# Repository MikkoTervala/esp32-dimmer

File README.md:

# esp32-dimmer

PCB for the ESP32 WROOM module, with power supply and up to six mosfets for LED strip dimming.

# 2023 Model

## Specifications

* Uses the ESP32-C3-WROOM-02-H4 microcontroller module
* Built in USB C connector for programming
* Designed to be made with SMD assembly
* 12 to 24V
* Designed for 5A single channel or 10A combined.

## Notes

* Ordering 10 PCB's with SMD assembly not including ESP32 cost 65€
* Ordering 10 ESP32-C3 modules and regulators cost 43€ 

## Next version ideas

* Add power LED
* Move 24V and GND pins to the middle of connector for shorter routing
* Expose all unused GPIO's as SMD test points

# 2020 Model

## Specifications

* 12 or 24V
* Designed for 5A single channel or 10A combined with a low cost 1 oz PCB.
* Can be used with ESP32-WROOM-32 module or the DOIT Esp32 DevKit available from china.
* Can be used with CUI VXO7803-500 DC-DC converter or with "mini power supply module 3A" available from china.
* Fits inside square european electrical box.

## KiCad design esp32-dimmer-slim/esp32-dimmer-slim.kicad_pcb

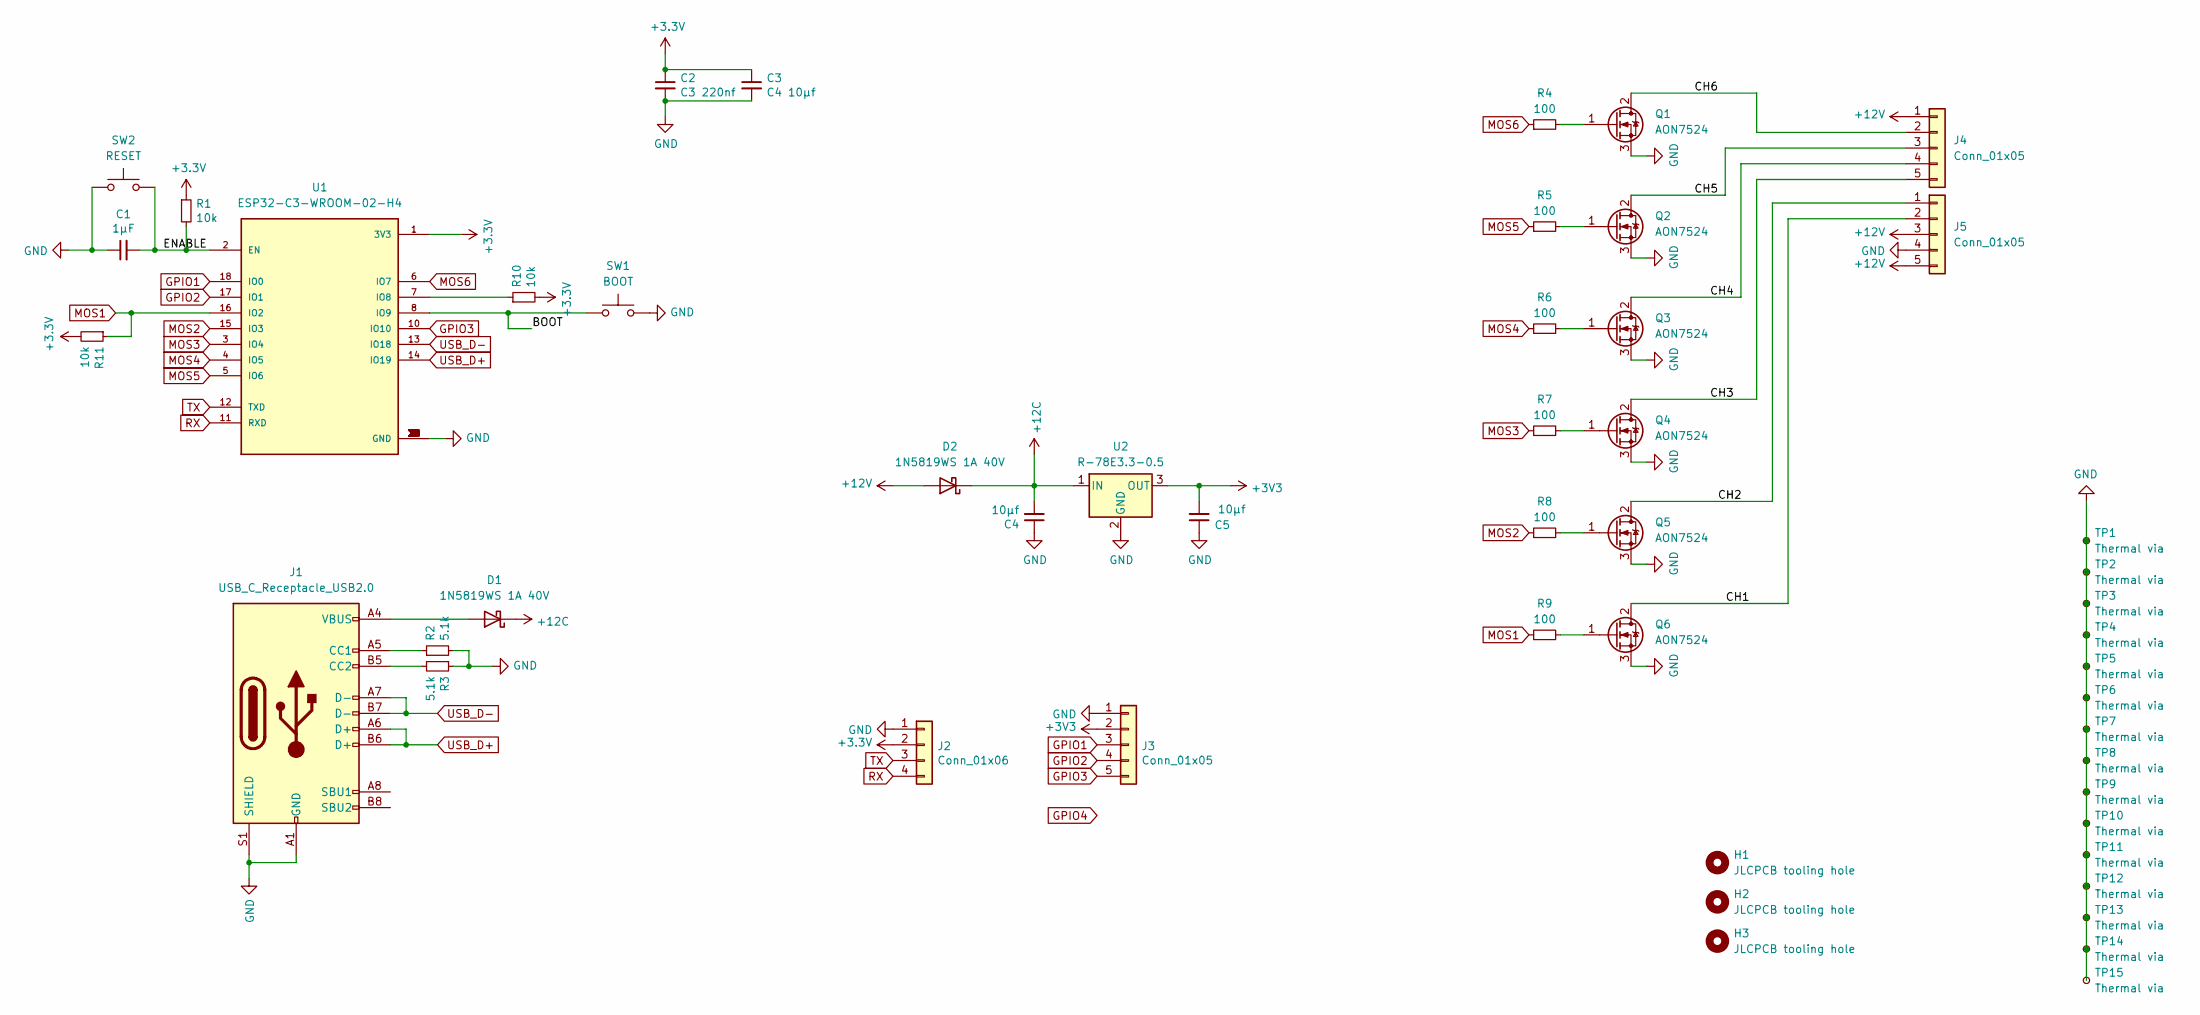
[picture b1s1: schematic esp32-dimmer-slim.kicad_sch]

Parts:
C1: 1µF; C_0603_1608Metric; LCSC Part # C15849
C2: C3 220nf; C_0603_1608Metric; LCSC Part # C21120
C3: C4 10µf; C_1206_3216Metric; LCSC Part # C13585
C4, C5: 10µf; C_1206_3216Metric; LCSC Part # C13585
D1, D2: 1N5819WS 1A 40V; D_SOD-323; LCSC Part # C191023
H1, H2, H3: JLCPCB tooling hole
J1: USB_C_Receptacle_USB2.0; TYPE-C-31-M-12; LCSC Part # C165948
J2: Conn_01x06; PinHeader_1x04_P2.54mm_Vertical
J3: Conn_01x05; PinHeader_1x05_P2.54mm_Vertical
J4, J5: Conn_01x05; CONN_2604-1105_WAG
Q1, Q2, Q3, Q4, Q5, Q6: AON7524; TRANS_AON7403; LCSC Part # C431195
R1, R10, R11: 10k; R_0603_1608Metric; LCSC Part # C25804
R2, R3: 5.1k; R_0603_1608Metric; LCSC Part # C23186
R4, R5, R6, R7, R8, R9: 100; R_0603_1608Metric; LCSC Part # C22775
SW1: BOOT; SW_Push_1P1T_XKB_TS-1187A; LCSC Part # C318884
SW2: RESET; SW_Push_1P1T_XKB_TS-1187A; LCSC Part # C318884
TP1, TP2, TP3, TP4, TP5, TP6, TP7, TP8, TP9, TP10, TP11, TP12, TP13, TP14, TP15: Thermal via; thermal via
U1: ESP32-C3-WROOM-02-H4; MODULE_ESP32-C3-WROOM-02-H4; LCSC Part # C2934560
U2: R-78E3.3-0.5; Converter_DCDC_RECOM_R-78E-0.5_THT

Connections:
+12C: C4.2, D1.1 (K), D2.1 (K), U2.1 (IN)
+12V: D2.2 (A), J4.1, J5.3, J5.5
/BOOT: SW1.1, U1.8 (IO9)
/CH1: J5.2, Q6.2 (D)
/CH2: J5.1, Q5.2 (D)
/CH3: J4.5, Q4.2 (D)
/CH4: J4.4, Q3.2 (D)
/CH5: J4.3, Q2.2 (D)
/CH6: J4.2, Q1.2 (D)
/ENABLE: C1.2, R1.2, SW2.2, U1.2 (EN)
GND: C1.1, C2.2, C3.2, C4.1, C5.1, J1.A1 (GND), J1.A12 (GND), J1.B1 (GND), J1.B12 (GND), J1.S1 (SHIELD), J2.1, J3.1, J5.4, Q1.3 (S), Q2.3 (S), Q3.3 (S), Q4.3 (S), Q5.3 (S), Q6.3 (S), R2.2, R3.1, SW1.2, SW2.1, TP1.1, TP2.1, TP3.1, TP4.1, TP5.1, TP6.1, TP7.1, TP8.1, TP9.1, TP10.1, TP11.1, TP12.1, TP13.1, TP14.1, TP15.1, U1.9 (GND), U1.19 (GND), U1.20 (GND), U1.21 (GND), U1.22 (GND), U1.23 (GND), U1.24 (GND), U1.25 (GND), U1.26 (GND), U1.27 (GND), U1.28 (GND), U1.29 (GND), U1.30 (GND), U1.31 (GND), U1.32 (GND), U1.33 (GND), U1.34 (GND), U1.35 (GND), U1.36 (GND), U1.37 (GND), U1.38 (GND), U1.39 (GND), U2.2 (GND)
GPIO1: J3.3, U1.18 (IO0)
GPIO2: J3.4, U1.17 (IO1)
GPIO3: J3.5, U1.10 (IO10)
MOS1: R9.1, R11.1, U1.16 (IO2)
MOS2: R8.1, U1.15 (IO3)
MOS3: R7.1, U1.3 (IO4)
MOS4: R6.1, U1.4 (IO5)
MOS5: R5.1, U1.5 (IO6)
MOS6: R4.1, U1.6 (IO7)
unnamed: D1.2 (A), J1.A4 (VBUS), J1.A9 (VBUS), J1.B4 (VBUS), J1.B9 (VBUS)
unnamed: J1.A5 (CC1), R2.1
unnamed: J1.B5 (CC2), R3.2
unnamed: Q1.1 (G), R4.2
unnamed: Q2.1 (G), R5.2
unnamed: Q3.1 (G), R6.2
unnamed: Q4.1 (G), R7.2
unnamed: Q5.1 (G), R8.2
unnamed: Q6.1 (G), R9.2
unnamed: R10.1, U1.7 (IO8)
RX: J2.4, U1.11 (RXD)
TX: J2.3, U1.12 (TXD)
USB_D+: J1.A6 (D+), J1.B6 (D+), U1.14 (IO19)
USB_D-: J1.A7 (D-), J1.B7 (D-), U1.13 (IO18)

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
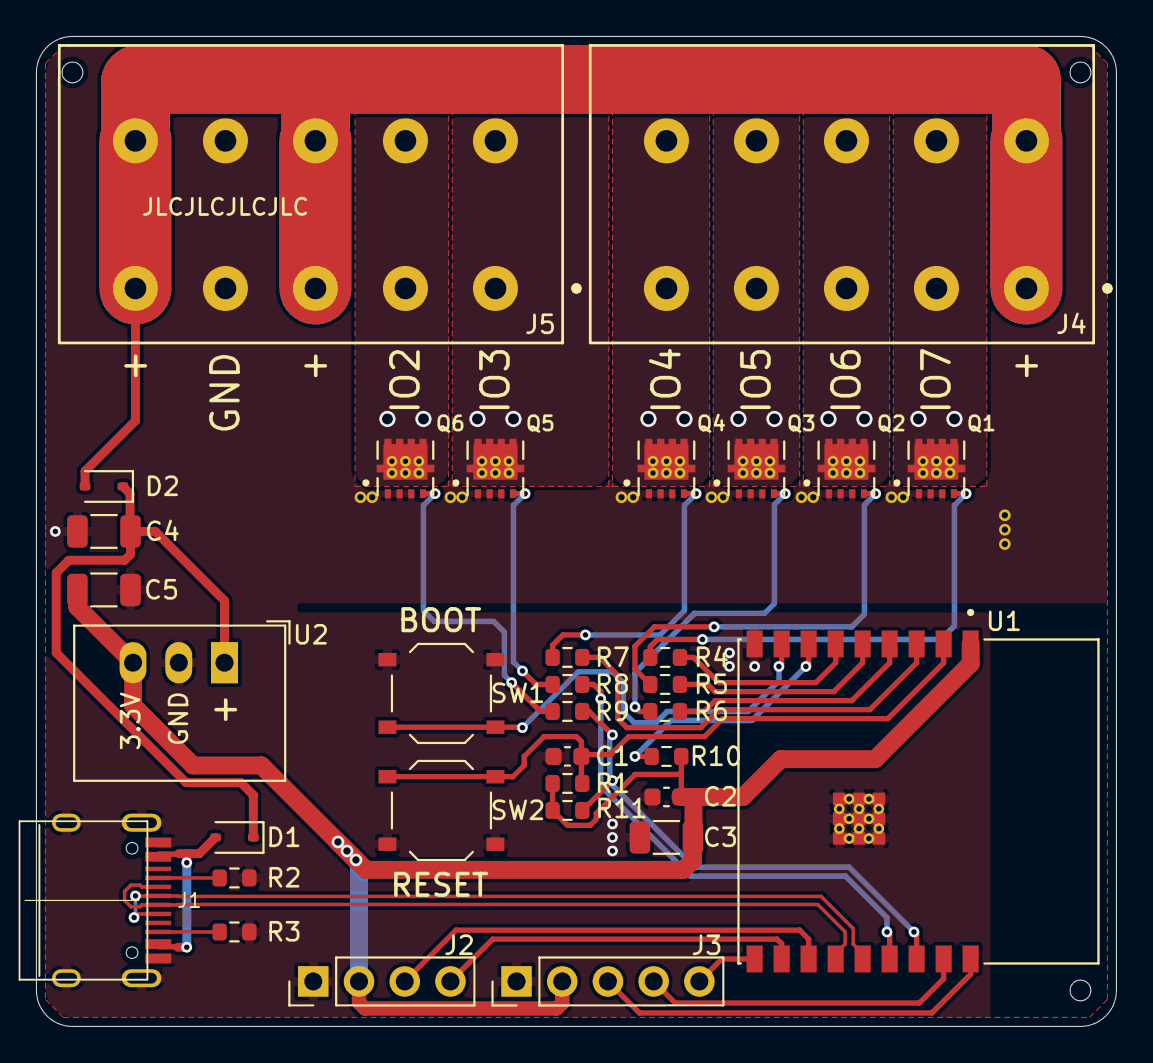
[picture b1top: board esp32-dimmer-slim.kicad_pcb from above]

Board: 2 copper layers, 60.0 x 55.0 mm, 51 parts (0 on the bottom side), 35 nets.

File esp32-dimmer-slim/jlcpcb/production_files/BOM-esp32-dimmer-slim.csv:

Comment,Designator,Footprint,LCSC
C4 10µf,"C3,C4,C5",C_1206_3216Metric,C13585
1µF,C1,C_0603_1608Metric,C15849
USB_C_Receptacle_USB2.0,J1,TYPE-C-31-M-12,C165948
1N5819WS 1A 40V,"D1,D2",D_SOD-323,C191023
C3 220nf,C2,C_0603_1608Metric,C21120
100,"R4,R5,R6,R7,R8,R9",R_0603_1608Metric,C22775
5.1k,"R2,R3",R_0603_1608Metric,C23186
10k,"R1,R10,R11",R_0603_1608Metric,C25804
BOOT,"SW1,SW2",SW_Push_1P1T_XKB_TS-1187A,C318884
AON7524,"Q1,Q2,Q3,Q4,Q5,Q6",TRANS_AON7403,C431195

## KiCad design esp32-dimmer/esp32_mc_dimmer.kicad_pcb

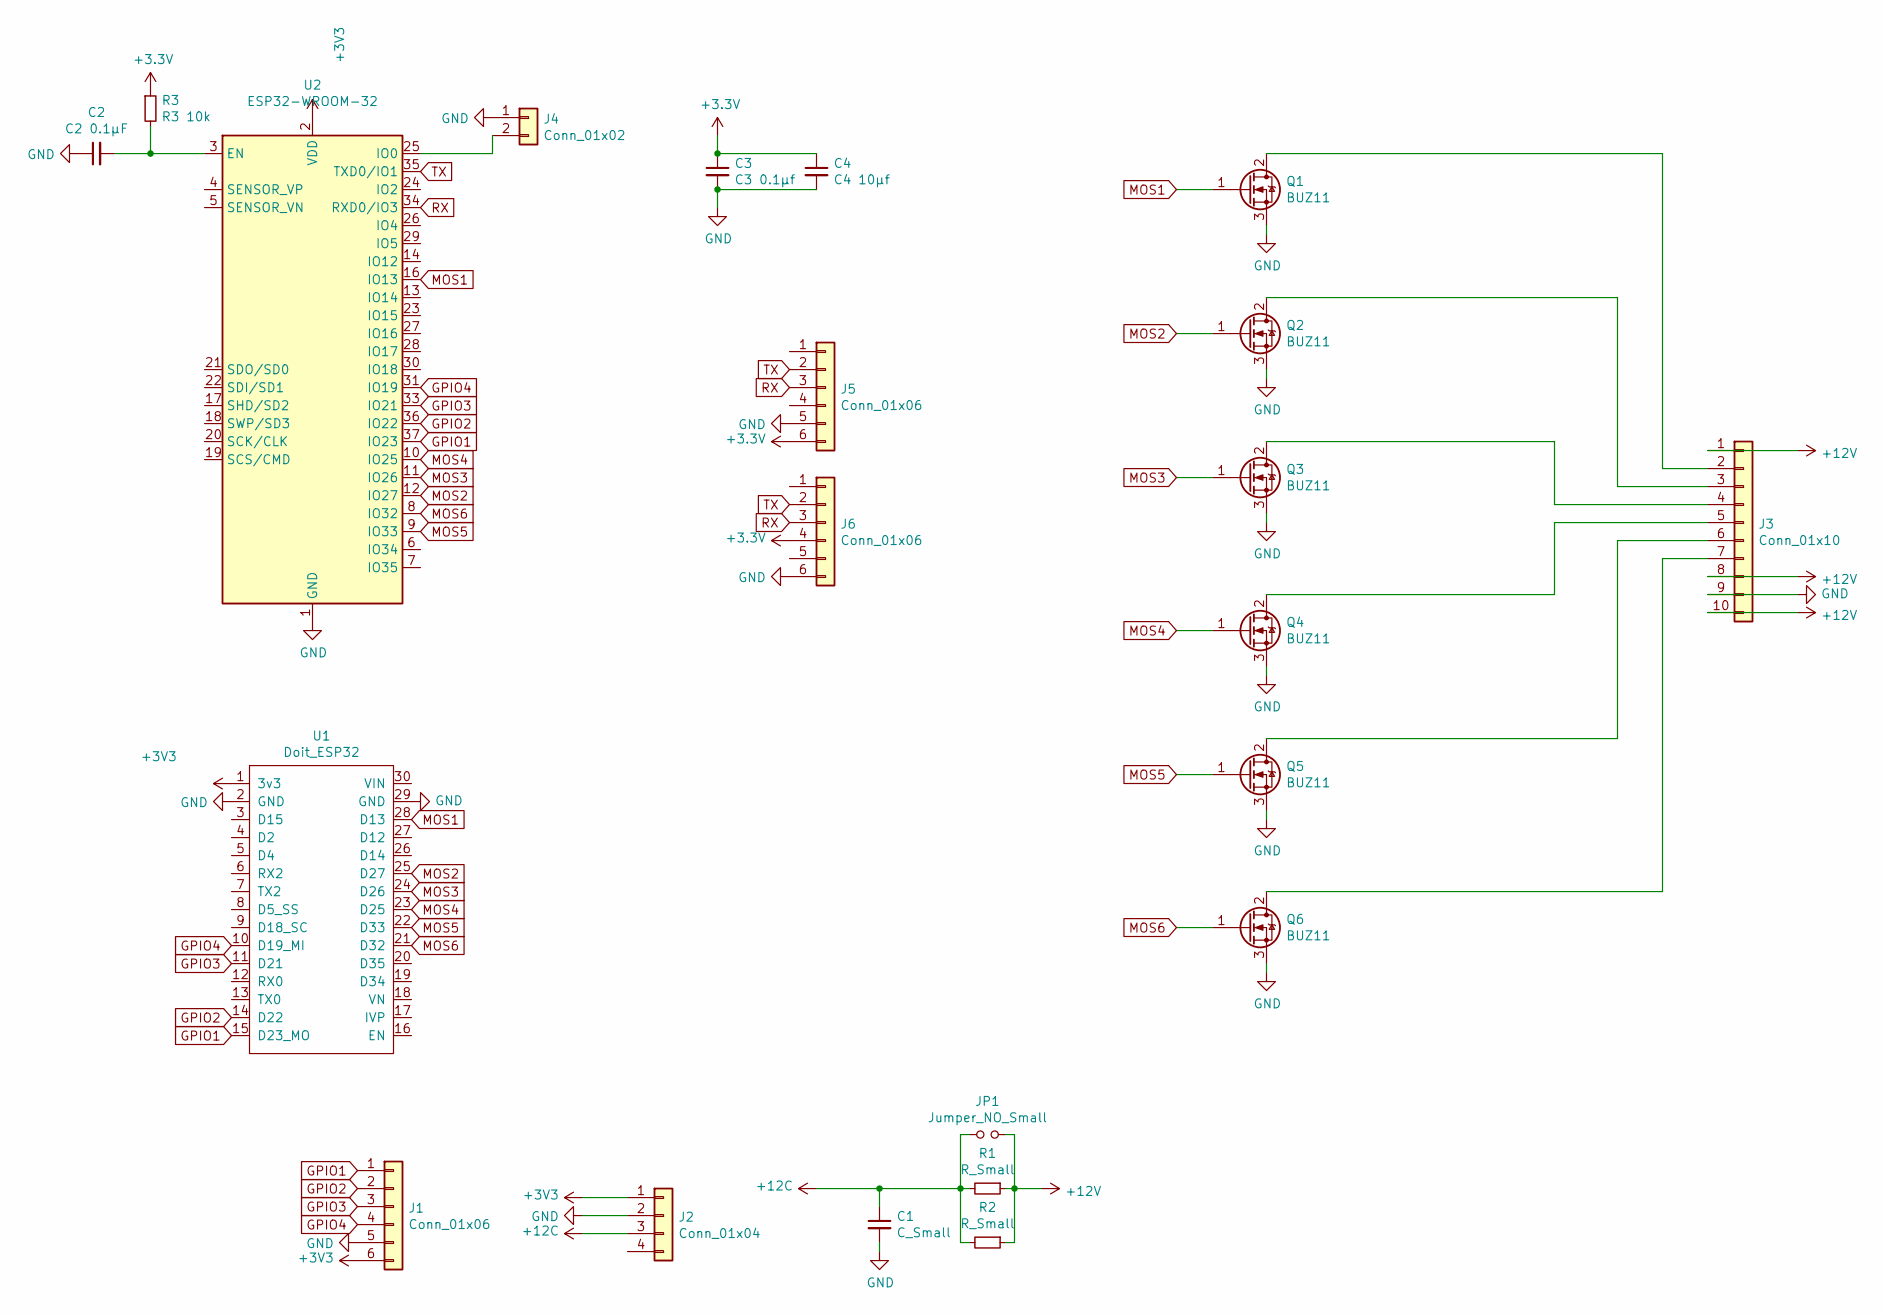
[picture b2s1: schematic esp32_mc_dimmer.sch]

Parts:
C1: C_Small; CP_Radial_D10.0mm_P2.50mm_P5.00mm
C2: C2 0.1µF; C_0805_2012Metric_Pad1.15x1.40mm_HandSolder
C3: C3 0.1µf; C_0805_2012Metric_Pad1.15x1.40mm_HandSolder
C4: C4 10µf; C_1210_3225Metric_Pad1.42x2.65mm_HandSolder
J1, J5, J6: Conn_01x06; PinHeader_1x06_P2.54mm_Vertical
J2: Conn_01x04; 4pin_reg_con
J3: Conn_01x10; Phoenix_SPTAF_1_10-5,0-EL
J4: Conn_01x02; PinHeader_1x02_P2.54mm_Vertical
JP1: Jumper_NO_Small; SolderJumper-2_P1.3mm_Open_TrianglePad1.0x1.5mm
Q1, Q2, Q3, Q4, Q5, Q6: BUZ11; TO-220-3_Vertical
R1: R_Small; R_0805_2012Metric_Pad1.15x1.40mm_HandSolder
R2: R_Small; R_Axial_DIN0411_L9.9mm_D3.6mm_P5.08mm_Vertical
R3: R3 10k; R_0805_2012Metric_Pad1.15x1.40mm_HandSolder
U1: Doit_ESP32
U2: ESP32-WROOM-32

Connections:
+12C: C1.1, J2.3, JP1.1, R1.2, R2.2
+12V: J3.1, J3.8, J3.10, JP1.2, R1.1, R2.1
GND: C1.2, C2.1, C3.2, C4.2, J1.5, J2.2, J3.9, J4.1, J5.5, J6.6, Q1.3 (S), Q2.3 (S), Q3.3 (S), Q4.3 (S), Q5.3 (S), Q6.3 (S), U1.2 (GND), U1.29 (GND), U2.1 (GND), U2.15 (GND), U2.38 (GND), U2.39 (GND)
GPIO1: J1.1, U1.15 (D23_MO), U2.37 (IO23)
GPIO2: J1.2, U1.14 (D22), U2.36 (IO22)
GPIO3: J1.3, U1.11 (D21), U2.33 (IO21)
GPIO4: J1.4, U1.10 (D19_MI), U2.31 (IO19)
MOS1: Q1.1 (G), U1.28 (D13), U2.16 (IO13)
MOS2: Q2.1 (G), U1.25 (D27), U2.12 (IO27)
MOS3: Q3.1 (G), U1.24 (D26), U2.11 (IO26)
MOS4: Q4.1 (G), U1.23 (D25), U2.10 (IO25)
MOS5: Q5.1 (G), U1.22 (D33), U2.9 (IO33)
MOS6: Q6.1 (G), U1.21 (D32), U2.8 (IO32)
unnamed: C2.2, R3.2, U2.3 (EN)
unnamed: J3.2, Q1.2 (D)
unnamed: J3.3, Q2.2 (D)
unnamed: J3.4, Q3.2 (D)
unnamed: J3.5, Q4.2 (D)
unnamed: J3.6, Q5.2 (D)
unnamed: J3.7, Q6.2 (D)
unnamed: J4.2, U2.25 (IO0)
RX: J5.3, J6.3, U2.34 (RXD0/IO3)
TX: J5.2, J6.2, U2.35 (TXD0/IO1)

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
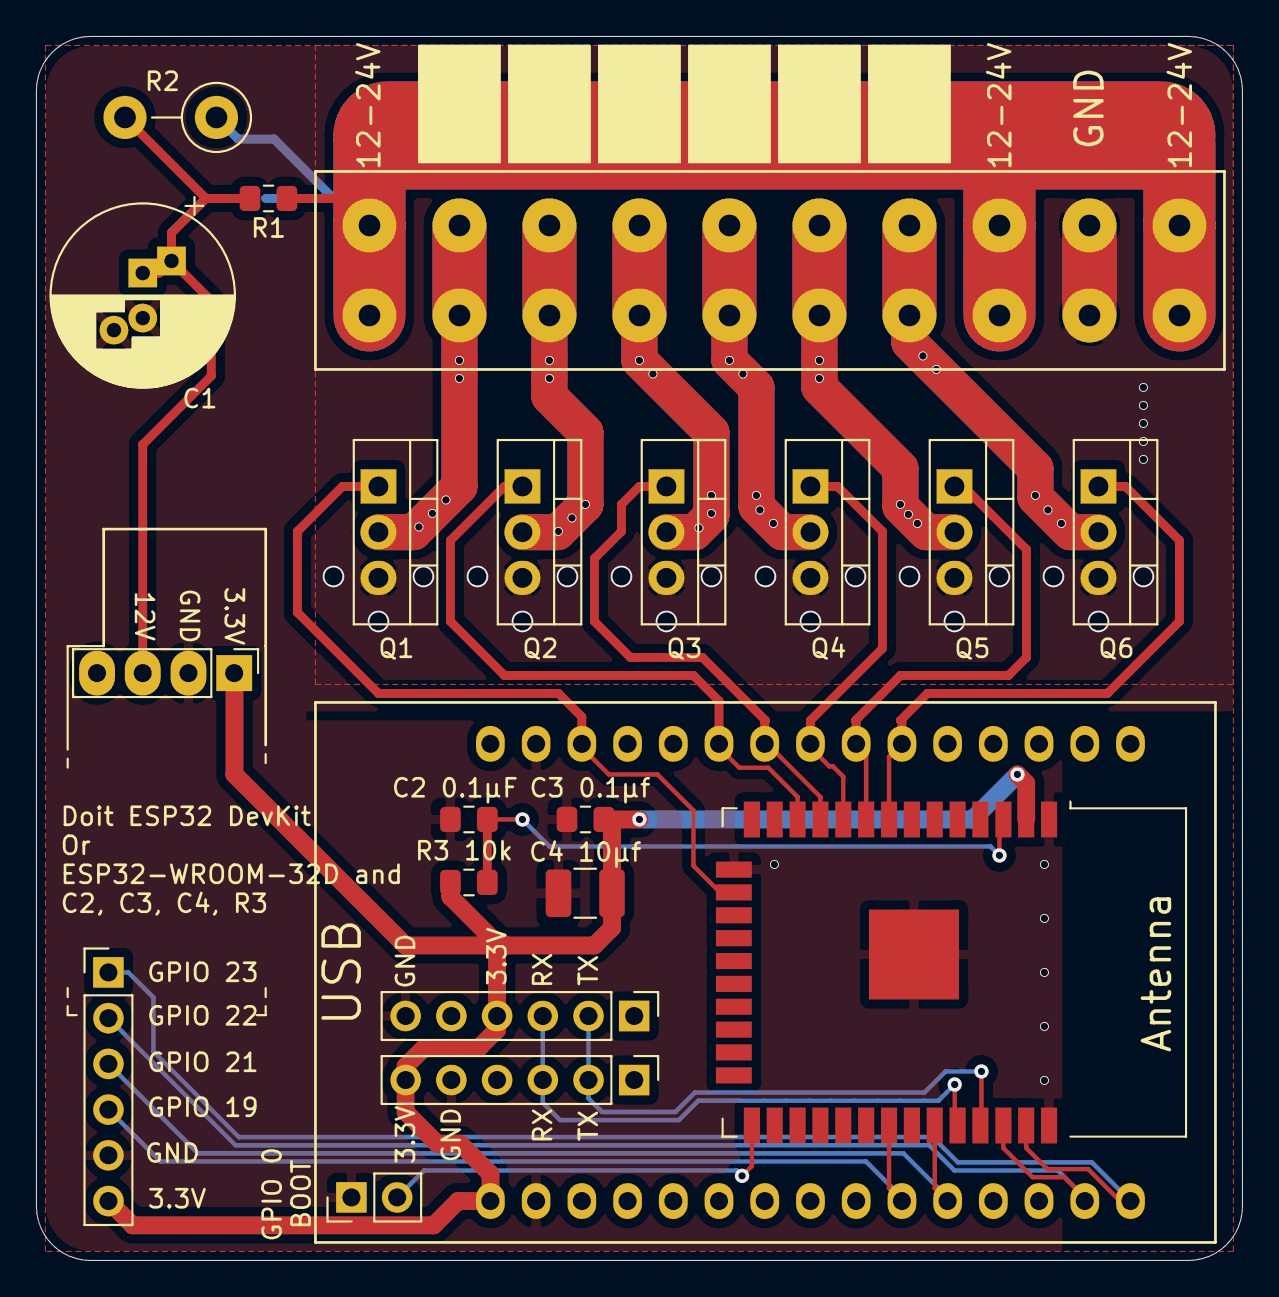
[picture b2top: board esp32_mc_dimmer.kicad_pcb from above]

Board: 2 copper layers, 67.0 x 68.0 mm, 22 parts (1 on the bottom side), 24 nets.

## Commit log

2020-12-04 add bom
2020-12-08 fix bom
2020-12-08 quick bom hotfix
2020-12-08 add bom (#1)
    * add bom
    * fix bom
    * quick bom hotfix
2020-12-08 Add relative libraries
2020-12-08 Add screenshots
2020-12-08 Add new psu module and improve power layout
2020-12-08 Update gerber files
2020-12-08 Change resistor to lower inrush
2023-10-13 Update gitignore for new version of kicad
2023-10-13 Add new libraries for 2023 model
2023-10-13 Add 2023 model
2023-11-21 Add pictures and specs of 2023 model
